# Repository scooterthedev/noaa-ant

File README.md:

# NOAAmp - Reliable Signal Gain for NOAA Reception
## By: @Scooter Y
### What it is?
NOAAmp is an extremely small PCB- only 28.5x20mm in size, that is capable of taking in an SMA input signal from an antenna like a custom built QFH antenna, and amplifing the signal to be sent to a device like a RTL-SDR to be viewed. This PCB will **only work for 137MHZ** since that is the freq of the NOAA-19 satellite that I am targeting. 

### Progress
This PCB + Enclousure is done, but you can view my journal throughout on JOURNAL.md.

### Photos!

### BOM
| Item Name                                           | Quanitiy   | Price   | Links:                                                                                                   |
|:----------------------------------------------------|:-------------|:-------------|:---------------------------------------------------------------------------------------------------------|
| Total for PCB including shipping                    | x1          | $65.26       |                                                                                                       |
| Enclosure (custom built)                            | x1           | around $45   | JLCCNC                                                                                                   |
| RTL-SDR                                             | x1           | $45          | https://www.amazon.ca/Nooelec-NESDR-SMArt-SDR-R820T2-Based/dp/B01HA642SW                                 |
| 2inch PVC cap                                       | x1           | $2           | Homedepot                                                                                                |
| 4inch x 10 feet PVC pipe                            | x1           | $20          | Homedepot                                                                                                |
| 1/2inch x 10feet PVC pipe                           | x1           | $4           | Homedepot                                                                                                |
| RG56 Coaxial Cable                                  | x1           | $19          | https://www.amazon.ca/YOTENKO-Extension-Bulkhead-Cellular-Receiver/dp/B0BM45DC3D                         |
| 12guage 15FT copper cable                           | x1           | $24          | https://www.homedepot.com/p/Southwire-15-ft-12-2-Solid-Romex-SIMpull-CU-NM-B-W-G-Wire-28828226/202210508 |
| PVC Cement                           | x1           | $6          | [https://www.homedepot.com/p/Southwire-15-ft-12-2-Solid-Romex-SIMpull-CU-NM-B-W-G-Wire-28828226/202210508](https://www.homedepot.ca/product/ipex-pvc-cement-04-low-voc-118ml/1001534394) |
| Screws                           | Apperantly MOQ is 25, so 25 it is           | $27.39          | [[https://www.homedepot.com/p/Southwire-15-ft-12-2-Solid-Romex-SIMpull-CU-NM-B-W-G-Wire-28828226/202210508](https://www.homedepot.ca/product/ipex-pvc-cement-04-low-voc-118ml/1001534394)](https://www.mcmaster.com/91864A002/?utm_term=socket+head+screws&location=9000797&matchtype=p&placement=&gad_source=1) |
| Total for everything including PCB + tax + shipping |              | ~257.65USD   |                                                                                                       |

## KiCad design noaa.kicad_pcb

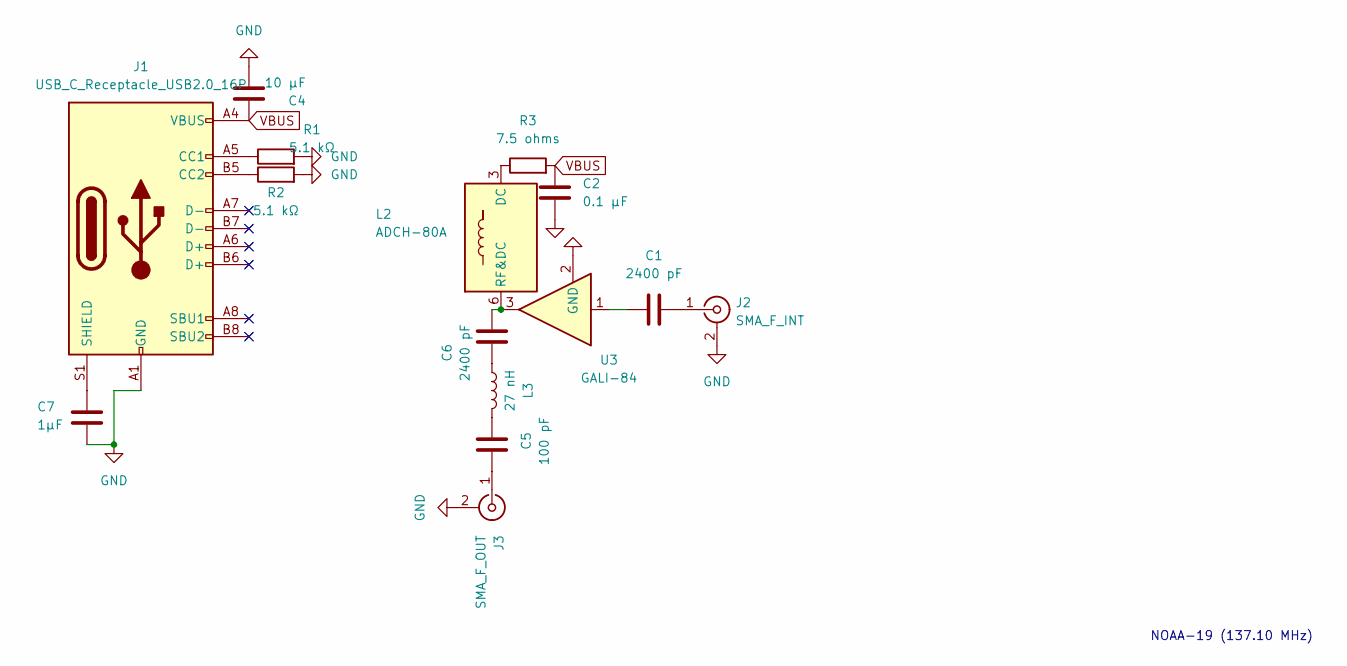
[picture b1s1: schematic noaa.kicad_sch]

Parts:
C1, C6: 2400 pF; C_0603_1608Metric
C2: 0.1 μF; C_0603_1608Metric
C4: 10 μF; C_0603_1608Metric
C5: 100 pF; C_0603_1608Metric
C7: 1µF; C_0603_1608Metric
J1: USB_C_Receptacle_USB2.0_16P; USB_C_Receptacle_GCT_USB4105-xx-A_16P_TopMnt_Horizontal
J2: SMA_F_INT; SMA_Amphenol_901-143_Horizontal
J3: SMA_F_OUT; SMA_Amphenol_901-143_Horizontal
L2: ADCH-80A; Mini-Circuits_CD542_H2.84mm
L3: 27 nH; L_0603_1608Metric
R1, R2: 5.1 kΩ; R_0603_1608Metric
R3: 7.5 ohms; R_0603_1608Metric
U3: GALI-84; SOT-89-3

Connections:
GND: C2.1, C4.1, C7.2, J1.A1 (GND), J1.A12 (GND), J1.B1 (GND), J1.B12 (GND), J2.2 (Ext), J3.2 (Ext), R1.2, R2.2, U3.2 (GND)
unnamed: C1.1, U3.1
unnamed: C5.2, L3.2
unnamed: C6.1, L3.1
unnamed: J1.A5 (CC1), R1.1
unnamed: J1.B5 (CC2), R2.1
unnamed: C7.1, J1.S1 (SHIELD)
unnamed: C1.2, J2.1 (In)
unnamed: C5.1, J3.1 (In)
unnamed: L2.3 (DC), R3.1
unnamed: C6.2, L2.6 (RF&DC), U3.3
VBUS: C2.2, C4.2, J1.A4 (VBUS), J1.A9 (VBUS), J1.B4 (VBUS), J1.B9 (VBUS), R3.2

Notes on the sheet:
NOAA-19 (137.10 MHz)

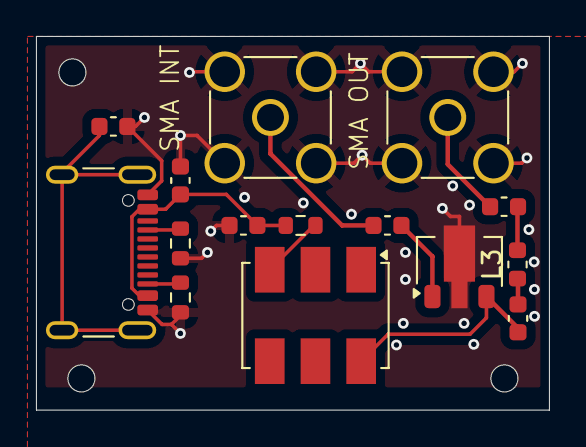
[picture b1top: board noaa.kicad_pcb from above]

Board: 2 copper layers, 28.5 x 20.8 mm, 15 parts (0 on the bottom side), 12 nets.

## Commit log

2025-06-05 Pretty sure I added all the parts for this
2025-06-05 Added most of the schematic wiring. Still need to do some USB ground and ESD protections
2025-06-05 Added the ability to switch between freq's for different NOAA's
2025-06-06 Schematic done!
2025-06-08 Fixed the RF amplified shematic. Time to wire!
2025-06-08 Routing should be done
2025-06-08 Did some ground stitching and added prod files
2025-06-08 Finished JOURNAL.md
2025-06-08 Added images
2025-06-09 Mounting holes x3 + STEP File
2025-06-12 Added my case that took a full day to make :(
2025-06-15 Switched it to top + bottom
2025-06-15 Useless
2025-06-15 Added BOM
2025-06-15 Added the case photo
2025-06-15 Added Day 3
2025-06-15 Added screws to the BOM
2025-06-16 Added BOM.csv
